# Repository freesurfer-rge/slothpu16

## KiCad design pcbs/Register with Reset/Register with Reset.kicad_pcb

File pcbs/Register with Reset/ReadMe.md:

# Register with Reset

This is a 16-bit register, which will reset to zero on power on, or when the RESET line is pulled low.

Notes:

- Diodes (but not LEDs) appeared to be back-to-front in placement files
- Had to resize vias, since smallest ones are extra cost
- RESET needs to be low for about 0.1 sec to be effective. On return high, need to wait about 0.1 sec before register will be effective again
- There is still some oddness around the RESET line on the r1 board; I've noticed that when the final test completes, there's often one LED left on. But a manual reset gets rid of it

Errata:

- The CLK and RESET lines block each other, since the clock signal to the registers is the result of ORing the two (well, delay-inverted-output for RESET) together. UPDATE for *r1*, the RESET and CLK lines are ANDed together to produce the 'clock' side of the reset, so a low on RESET will inhibit the clock, and should largely avoid this issue.

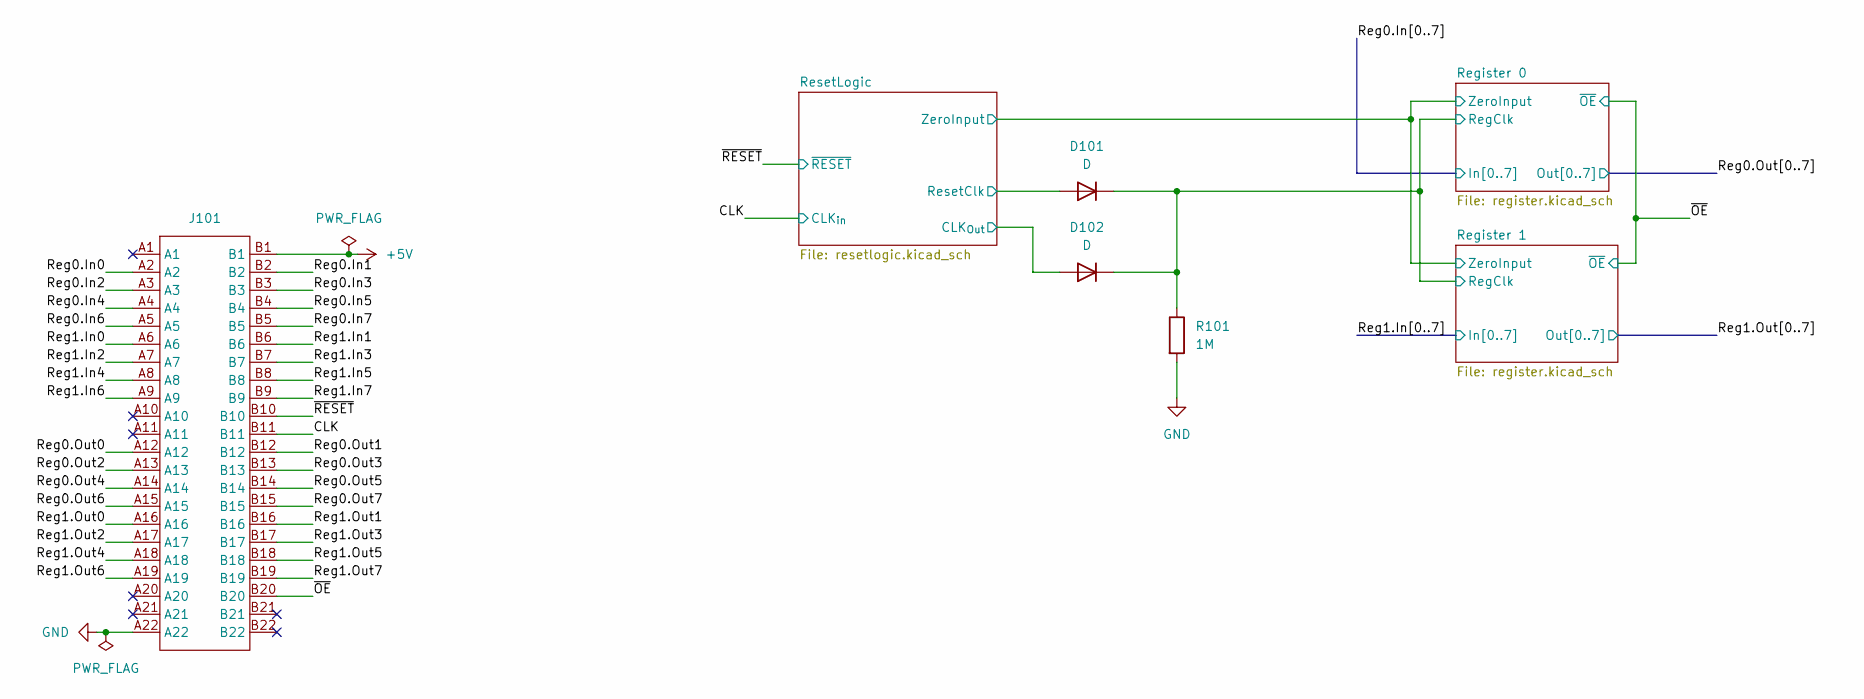
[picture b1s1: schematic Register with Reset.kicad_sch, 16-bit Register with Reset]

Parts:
D101, D102: D; D_SOD-123; LCSC C7420318
J101: TE-5530843-4-Edge
R101: 1M; R_0603_1608Metric; LCSC C22935

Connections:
+5V: J101.B1; also elsewhere on the board
/CLK: J101.B11; also elsewhere on the board
/Reg0.In0: J101.A2; also elsewhere on the board
/Reg0.In1: J101.B2; also elsewhere on the board
/Reg0.In2: J101.A3; also elsewhere on the board
/Reg0.In3: J101.B3; also elsewhere on the board
/Reg0.In4: J101.A4; also elsewhere on the board
/Reg0.In5: J101.B4; also elsewhere on the board
/Reg0.In6: J101.A5; also elsewhere on the board
/Reg0.In7: J101.B5; also elsewhere on the board
/Reg0.Out0: J101.A12; also elsewhere on the board
/Reg0.Out1: J101.B12; also elsewhere on the board
/Reg0.Out2: J101.A13; also elsewhere on the board
/Reg0.Out3: J101.B13; also elsewhere on the board
/Reg0.Out4: J101.A14; also elsewhere on the board
/Reg0.Out5: J101.B14; also elsewhere on the board
/Reg0.Out6: J101.A15; also elsewhere on the board
/Reg0.Out7: J101.B15; also elsewhere on the board
/Reg1.In0: J101.A6; also elsewhere on the board
/Reg1.In1: J101.B6; also elsewhere on the board
/Reg1.In2: J101.A7; also elsewhere on the board
/Reg1.In3: J101.B7; also elsewhere on the board
/Reg1.In4: J101.A8; also elsewhere on the board
/Reg1.In5: J101.B8; also elsewhere on the board
/Reg1.In6: J101.A9; also elsewhere on the board
/Reg1.In7: J101.B9; also elsewhere on the board
/Reg1.Out0: J101.A16; also elsewhere on the board
/Reg1.Out1: J101.B16; also elsewhere on the board
/Reg1.Out2: J101.A17; also elsewhere on the board
/Reg1.Out3: J101.B17; also elsewhere on the board
/Reg1.Out4: J101.A18; also elsewhere on the board
/Reg1.Out5: J101.B18; also elsewhere on the board
/Reg1.Out6: J101.A19; also elsewhere on the board
/Reg1.Out7: J101.B19; also elsewhere on the board
/Register 0/RegClk: D101.1 (K), D102.1 (K), R101.1; also elsewhere on the board
/ResetLogic/CLK_{Out}: D102.2 (A); also elsewhere on the board
/ResetLogic/ResetClk: D101.2 (A); also elsewhere on the board
/~OE: J101.B20; also elsewhere on the board
/~RESET: J101.B10; also elsewhere on the board
GND: J101.A22, R101.2; also elsewhere on the board

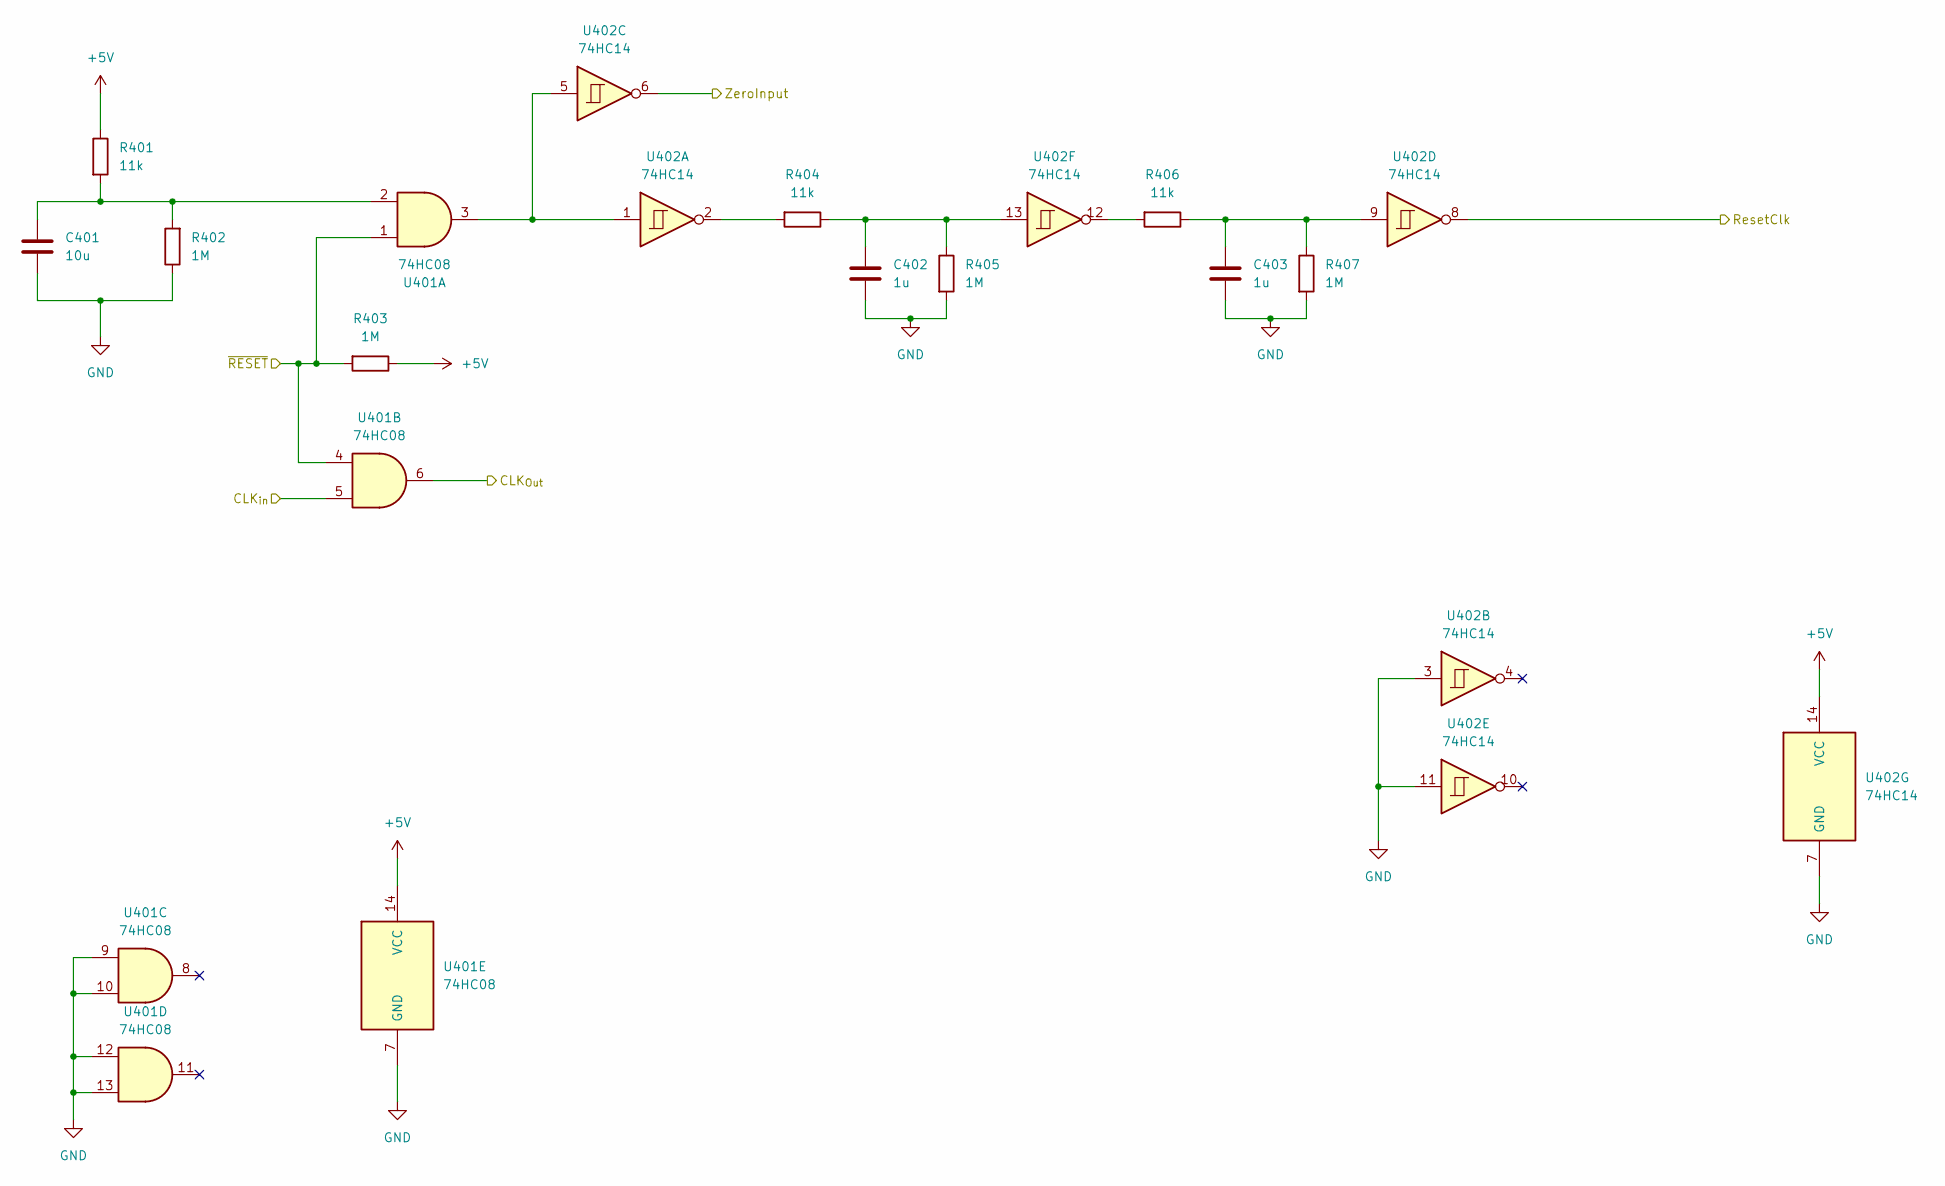
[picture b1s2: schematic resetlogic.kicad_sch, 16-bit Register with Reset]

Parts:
C401: 10u; C_0603_1608Metric; LCSC C19702
C402, C403: 1u; C_0603_1608Metric; LCSC C15849
R401, R404, R406: 11k; R_0603_1608Metric; LCSC C25950
R402, R403, R405, R407: 1M; R_0603_1608Metric; LCSC C22935
U401: 74HC08; SOIC-14_3.9x8.7mm_P1.27mm; LCSC C5593
U402: 74HC14; SOIC-14_3.9x8.7mm_P1.27mm; LCSC C5605

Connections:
+5V: R401.1, R403.1, U401.14 (VCC), U402.14 (VCC); also elsewhere on the board
/CLK: U401.5; also elsewhere on the board
/Register 0/ZeroInput: U402.6; also elsewhere on the board
/ResetLogic/CLK_{Out}: U401.6; also elsewhere on the board
/ResetLogic/ResetClk: U402.8; also elsewhere on the board
/~RESET: R403.2, U401.1, U401.4; also elsewhere on the board
GND: C401.2, C402.2, C403.2, R402.1, R405.2, R407.2, U401.7 (GND), U401.9, U401.10, U401.12, U401.13, U402.3, U402.7 (GND), U402.11; also elsewhere on the board
unnamed: C401.1, R401.2, R402.2, U401.2
unnamed: C402.1, R404.1, R405.1, U402.13
unnamed: C403.1, R406.1, R407.1, U402.9
unnamed: R404.2, U402.2
unnamed: R406.2, U402.12
unnamed: U401.3, U402.1, U402.5

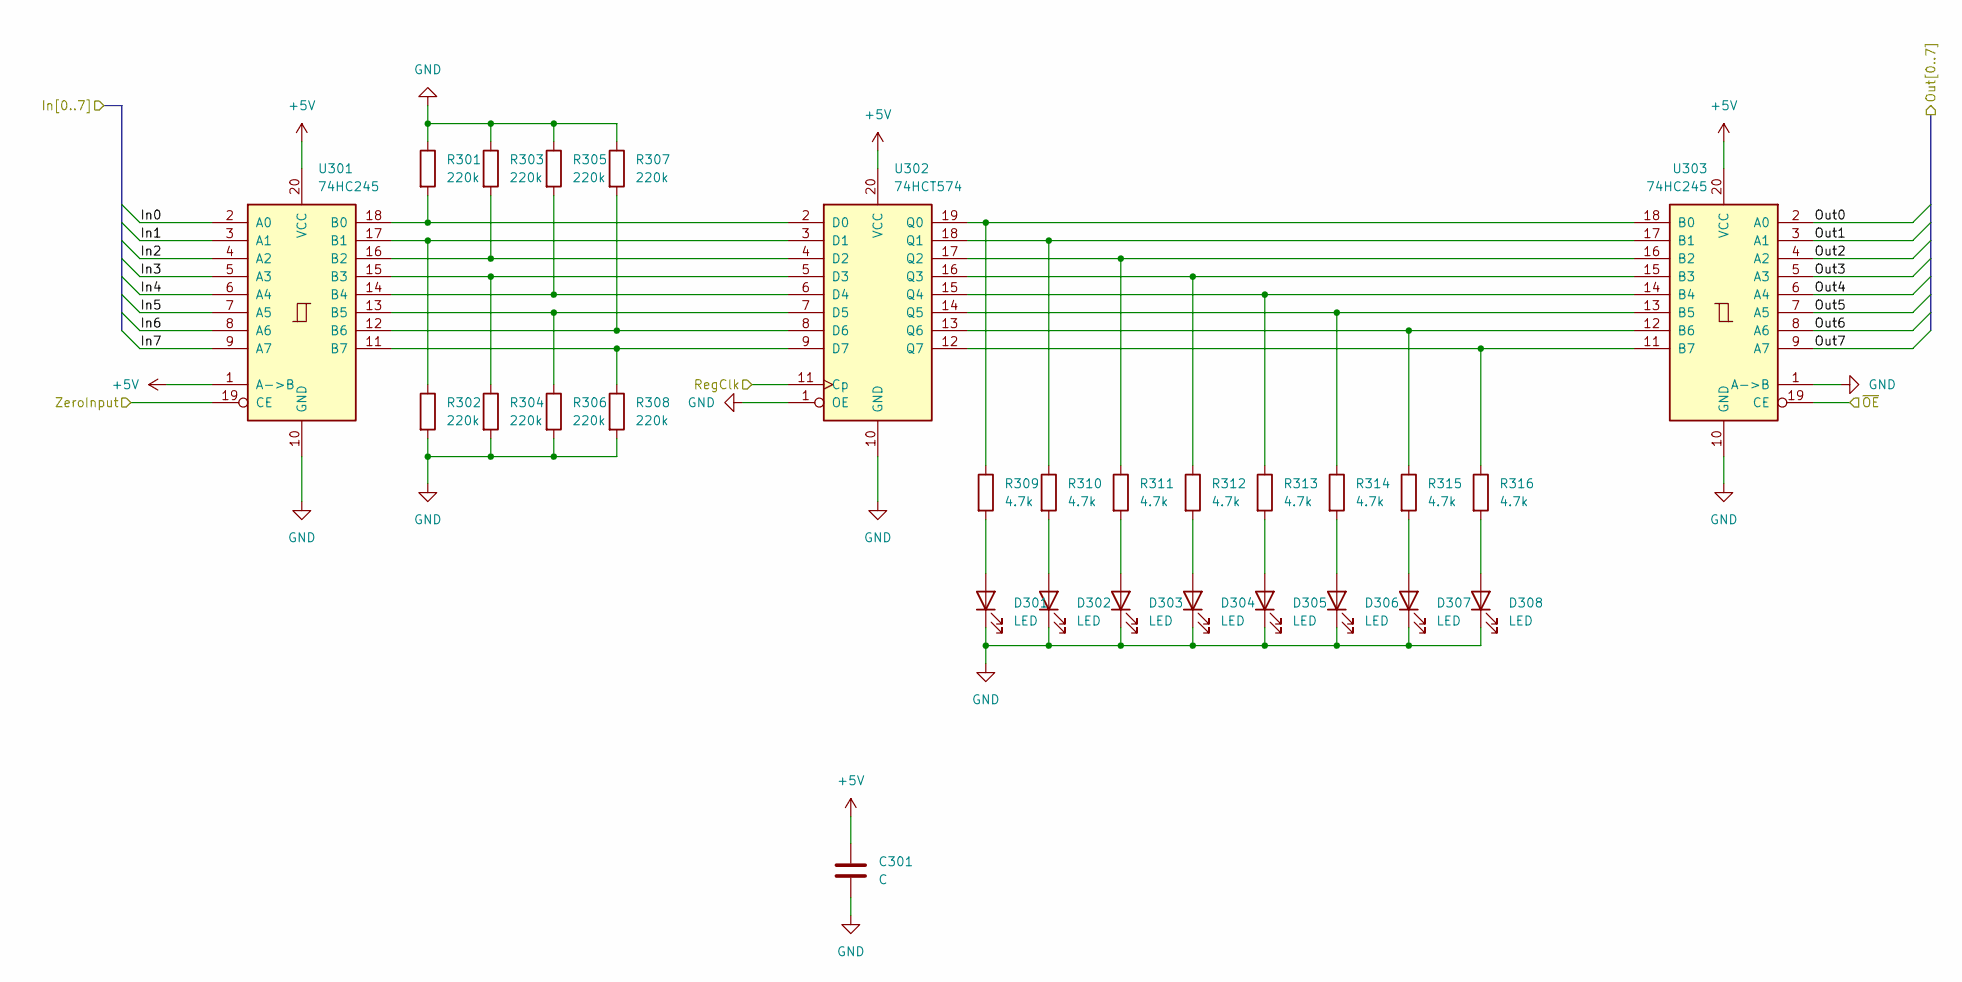
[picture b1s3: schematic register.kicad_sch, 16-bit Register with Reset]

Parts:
C301: C; C_0603_1608Metric; LCSC C14663
D301, D302, D303, D304, D305, D306, D307, D308: LED; LED_0603_1608Metric; LCSC C2290
R301, R302, R303, R304, R305, R306, R307, R308: 220k; R_0603_1608Metric; LCSC C22961
R309, R310, R311, R312, R313, R314, R315, R316: 4.7k; R_0603_1608Metric; LCSC C23162
U301, U303: 74HC245; SOIC-20W_7.5x12.8mm_P1.27mm; LCSC C5625
U302: 74HCT574; DIP-20_W7.62mm_Socket

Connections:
+5V: C301.1, U301.1 (A->B), U301.20 (VCC), U302.20 (VCC), U303.20 (VCC); also elsewhere on the board
/Reg1.In0: U301.2 (A0); also elsewhere on the board
/Reg1.In1: U301.3 (A1); also elsewhere on the board
/Reg1.In2: U301.4 (A2); also elsewhere on the board
/Reg1.In3: U301.5 (A3); also elsewhere on the board
/Reg1.In4: U301.6 (A4); also elsewhere on the board
/Reg1.In5: U301.7 (A5); also elsewhere on the board
/Reg1.In6: U301.8 (A6); also elsewhere on the board
/Reg1.In7: U301.9 (A7); also elsewhere on the board
/Reg1.Out0: U303.2 (A0); also elsewhere on the board
/Reg1.Out1: U303.3 (A1); also elsewhere on the board
/Reg1.Out2: U303.4 (A2); also elsewhere on the board
/Reg1.Out3: U303.5 (A3); also elsewhere on the board
/Reg1.Out4: U303.6 (A4); also elsewhere on the board
/Reg1.Out5: U303.7 (A5); also elsewhere on the board
/Reg1.Out6: U303.8 (A6); also elsewhere on the board
/Reg1.Out7: U303.9 (A7); also elsewhere on the board
/Register 0/RegClk: U302.11 (Cp); also elsewhere on the board
/Register 0/ZeroInput: U301.19 (CE); also elsewhere on the board
/~OE: U303.19 (CE); also elsewhere on the board
GND: C301.2, D301.1 (K), D302.1 (K), D303.1 (K), D304.1 (K), D305.1 (K), D306.1 (K), D307.1 (K), D308.1 (K), R301.1, R302.2, R303.1, R304.2, R305.1, R306.2, R307.1, R308.2, U301.10 (GND), U302.1 (OE), U302.10 (GND), U303.1 (A->B), U303.10 (GND); also elsewhere on the board
unnamed: D301.2 (A), R309.2
unnamed: D302.2 (A), R310.2
unnamed: D303.2 (A), R311.2
unnamed: D304.2 (A), R312.2
unnamed: D305.2 (A), R313.2
unnamed: D306.2 (A), R314.2
unnamed: D307.2 (A), R315.2
unnamed: D308.2 (A), R316.2
unnamed: R301.2, U301.18 (B0), U302.2 (D0)
unnamed: R302.1, U301.17 (B1), U302.3 (D1)
unnamed: R303.2, U301.16 (B2), U302.4 (D2)
unnamed: R304.1, U301.15 (B3), U302.5 (D3)
unnamed: R305.2, U301.14 (B4), U302.6 (D4)
unnamed: R306.1, U301.13 (B5), U302.7 (D5)
unnamed: R307.2, U301.12 (B6), U302.8 (D6)
unnamed: R308.1, U301.11 (B7), U302.9 (D7)
unnamed: R309.1, U302.19 (Q0), U303.18 (B0)
unnamed: R310.1, U302.18 (Q1), U303.17 (B1)
unnamed: R311.1, U302.17 (Q2), U303.16 (B2)
unnamed: R312.1, U302.16 (Q3), U303.15 (B3)
unnamed: R313.1, U302.15 (Q4), U303.14 (B4)
unnamed: R314.1, U302.14 (Q5), U303.13 (B5)
unnamed: R315.1, U302.13 (Q6), U303.12 (B6)
unnamed: R316.1, U302.12 (Q7), U303.11 (B7)

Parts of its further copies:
C201: C; C_0603_1608Metric; LCSC C14663
D201, D202, D203, D204, D205, D206, D207, D208: LED; LED_0603_1608Metric; LCSC C2290
R201, R202, R203, R204, R205, R206, R207, R208: 220k; R_0603_1608Metric; LCSC C22961
R209, R210, R211, R212, R213, R214, R215, R216: 4.7k; R_0603_1608Metric; LCSC C23162
U201, U203: 74HC245; SOIC-20W_7.5x12.8mm_P1.27mm; LCSC C5625
U202: 74HCT574; DIP-20_W7.62mm_Socket

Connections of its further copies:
+5V: C201.1, U201.1 (A->B), U201.20 (VCC), U202.20 (VCC), U203.20 (VCC); also elsewhere on the board
/Reg0.In0: U201.2 (A0); also elsewhere on the board
/Reg0.In1: U201.3 (A1); also elsewhere on the board
/Reg0.In2: U201.4 (A2); also elsewhere on the board
/Reg0.In3: U201.5 (A3); also elsewhere on the board
/Reg0.In4: U201.6 (A4); also elsewhere on the board
/Reg0.In5: U201.7 (A5); also elsewhere on the board
/Reg0.In6: U201.8 (A6); also elsewhere on the board
/Reg0.In7: U201.9 (A7); also elsewhere on the board
/Reg0.Out0: U203.2 (A0); also elsewhere on the board
/Reg0.Out1: U203.3 (A1); also elsewhere on the board
/Reg0.Out2: U203.4 (A2); also elsewhere on the board
/Reg0.Out3: U203.5 (A3); also elsewhere on the board
/Reg0.Out4: U203.6 (A4); also elsewhere on the board
/Reg0.Out5: U203.7 (A5); also elsewhere on the board
/Reg0.Out6: U203.8 (A6); also elsewhere on the board
/Reg0.Out7: U203.9 (A7); also elsewhere on the board
/Register 0/RegClk: U202.11 (Cp); also elsewhere on the board
/Register 0/ZeroInput: U201.19 (CE); also elsewhere on the board
/~OE: U203.19 (CE); also elsewhere on the board
GND: C201.2, D201.1 (K), D202.1 (K), D203.1 (K), D204.1 (K), D205.1 (K), D206.1 (K), D207.1 (K), D208.1 (K), R201.1, R202.2, R203.1, R204.2, R205.1, R206.2, R207.1, R208.2, U201.10 (GND), U202.1 (OE), U202.10 (GND), U203.1 (A->B), U203.10 (GND); also elsewhere on the board
unnamed: D201.2 (A), R209.2
unnamed: D202.2 (A), R210.2
unnamed: D203.2 (A), R211.2
unnamed: D204.2 (A), R212.2
unnamed: D205.2 (A), R213.2
unnamed: D206.2 (A), R214.2
unnamed: D207.2 (A), R215.2
unnamed: D208.2 (A), R216.2
unnamed: R201.2, U201.18 (B0), U202.2 (D0)
unnamed: R202.1, U201.17 (B1), U202.3 (D1)
unnamed: R203.2, U201.16 (B2), U202.4 (D2)
unnamed: R204.1, U201.15 (B3), U202.5 (D3)
unnamed: R205.2, U201.14 (B4), U202.6 (D4)
unnamed: R206.1, U201.13 (B5), U202.7 (D5)
unnamed: R207.2, U201.12 (B6), U202.8 (D6)
unnamed: R208.1, U201.11 (B7), U202.9 (D7)
unnamed: R209.1, U202.19 (Q0), U203.18 (B0)
unnamed: R210.1, U202.18 (Q1), U203.17 (B1)
unnamed: R211.1, U202.17 (Q2), U203.16 (B2)
unnamed: R212.1, U202.16 (Q3), U203.15 (B3)
unnamed: R213.1, U202.15 (Q4), U203.14 (B4)
unnamed: R214.1, U202.14 (Q5), U203.13 (B5)
unnamed: R215.1, U202.13 (Q6), U203.12 (B6)
unnamed: R216.1, U202.12 (Q7), U203.11 (B7)

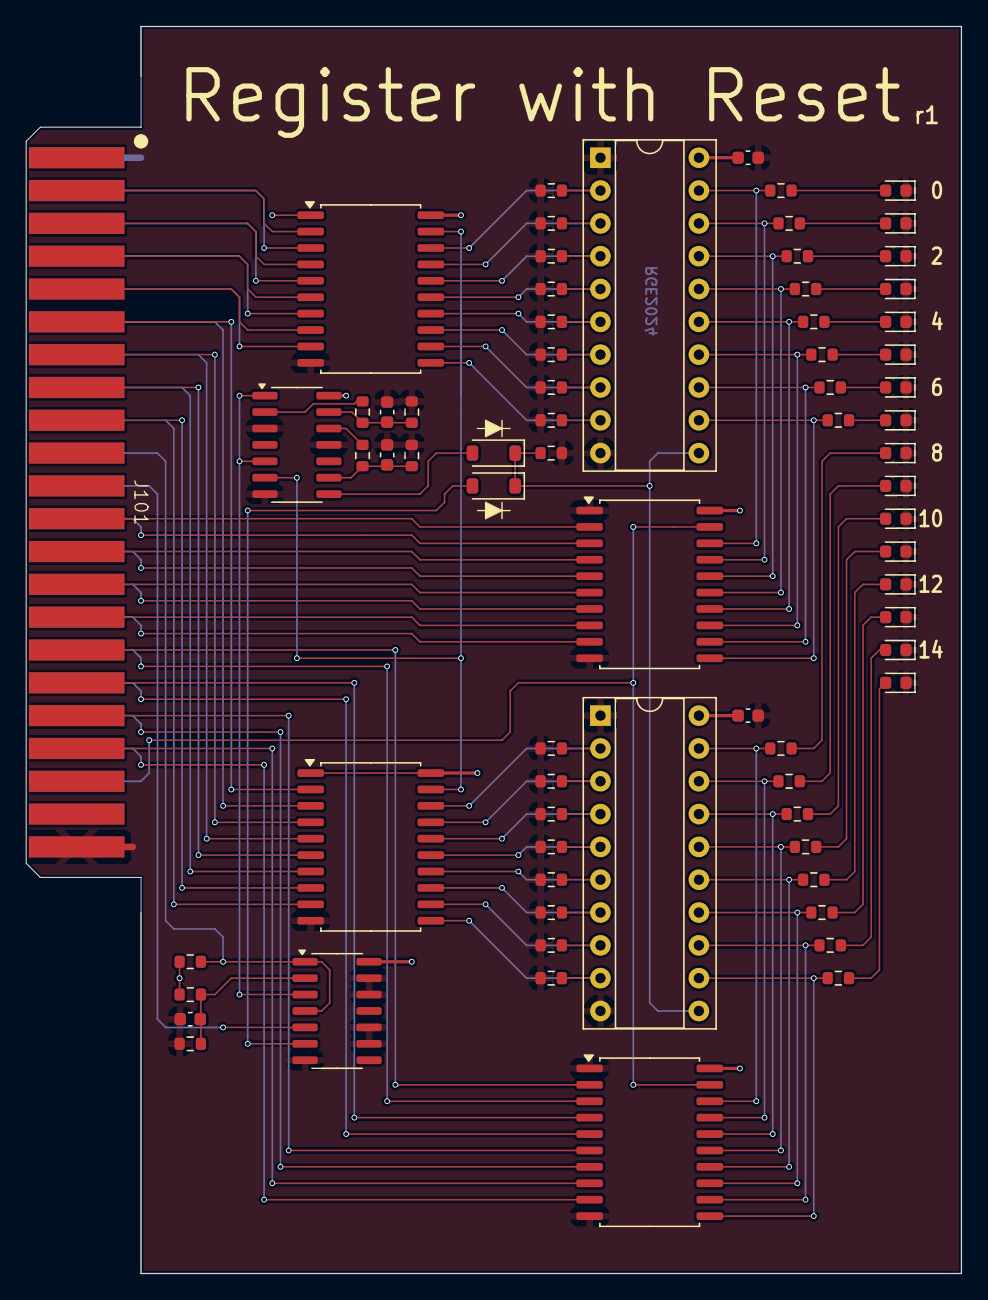
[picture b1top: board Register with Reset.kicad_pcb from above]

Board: 2 copper layers, 72.4 x 96.5 mm, 72 parts (0 on the bottom side), 95 nets.

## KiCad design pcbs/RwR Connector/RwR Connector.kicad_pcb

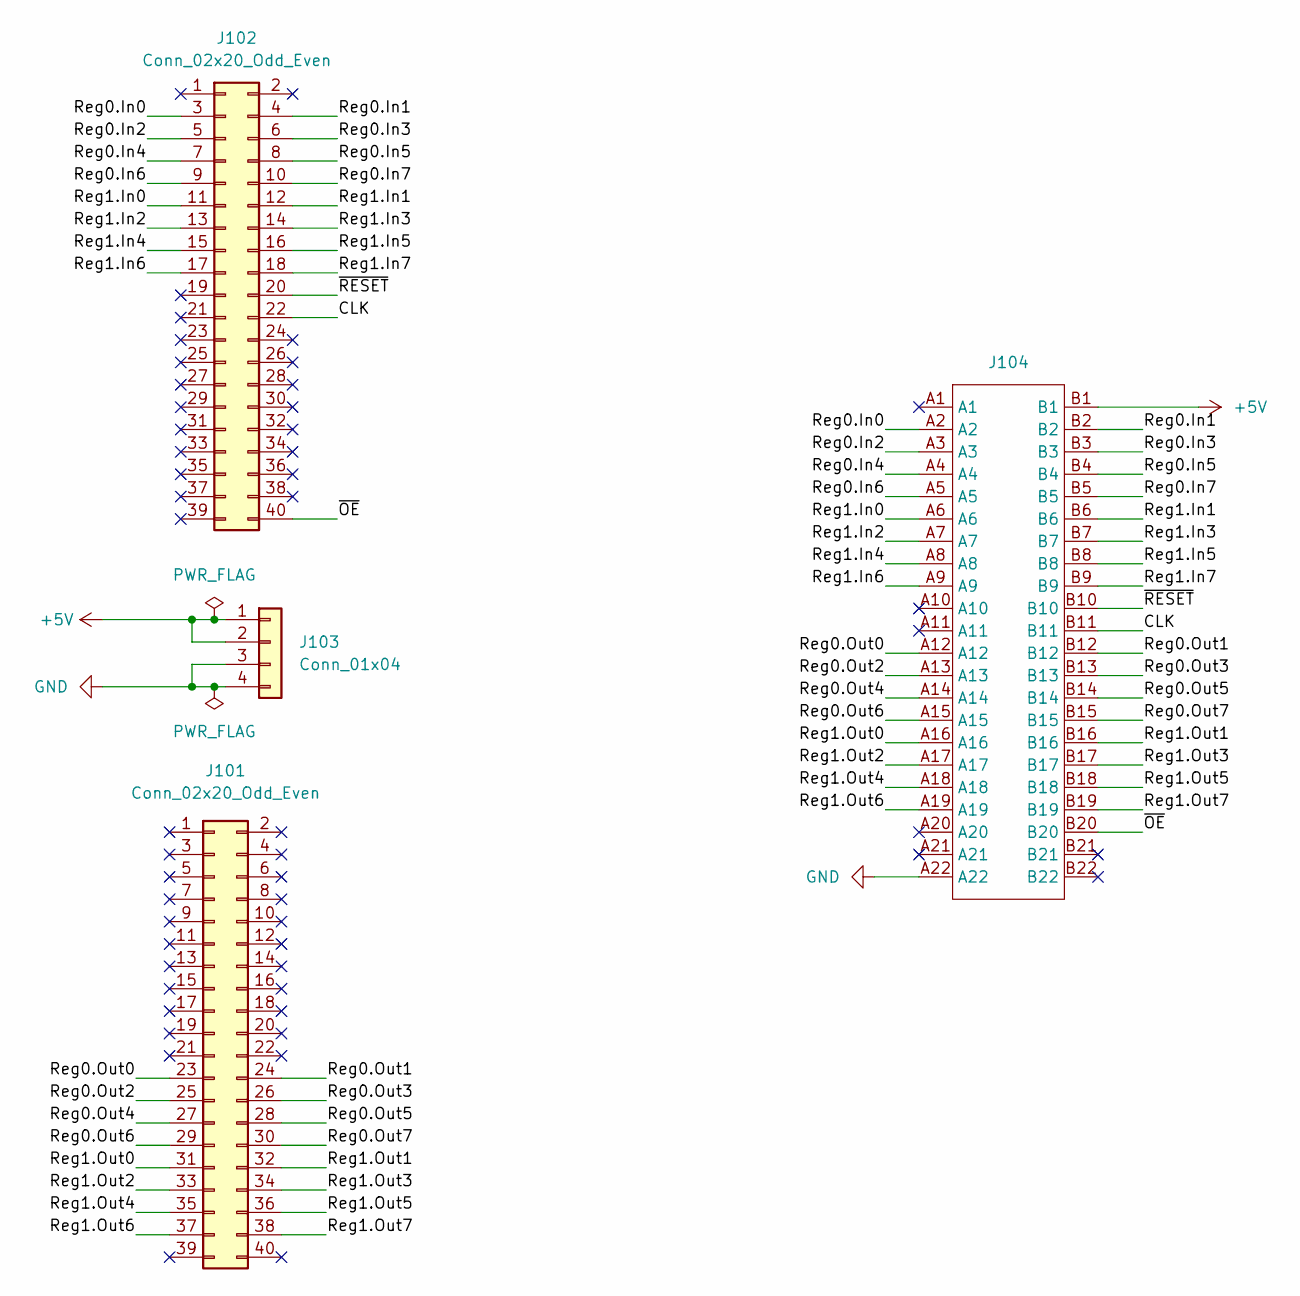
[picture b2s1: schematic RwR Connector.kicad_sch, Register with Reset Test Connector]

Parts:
J101, J102: Conn_02x20_Odd_Even; PinHeader_2x20_P2.54mm_Vertical
J103: Conn_01x04; PinHeader_1x04_P2.54mm_Vertical
J104: TE-5530843-4-Mount

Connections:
+5V: J103.1, J103.2, J104.B1
/CLK: J102.22, J104.B11
/Reg0.In0: J102.3, J104.A2
/Reg0.In1: J102.4, J104.B2
/Reg0.In2: J102.5, J104.A3
/Reg0.In3: J102.6, J104.B3
/Reg0.In4: J102.7, J104.A4
/Reg0.In5: J102.8, J104.B4
/Reg0.In6: J102.9, J104.A5
/Reg0.In7: J102.10, J104.B5
/Reg0.Out0: J101.23, J104.A12
/Reg0.Out1: J101.24, J104.B12
/Reg0.Out2: J101.25, J104.A13
/Reg0.Out3: J101.26, J104.B13
/Reg0.Out4: J101.27, J104.A14
/Reg0.Out5: J101.28, J104.B14
/Reg0.Out6: J101.29, J104.A15
/Reg0.Out7: J101.30, J104.B15
/Reg1.In0: J102.11, J104.A6
/Reg1.In1: J102.12, J104.B6
/Reg1.In2: J102.13, J104.A7
/Reg1.In3: J102.14, J104.B7
/Reg1.In4: J102.15, J104.A8
/Reg1.In5: J102.16, J104.B8
/Reg1.In6: J102.17, J104.A9
/Reg1.In7: J102.18, J104.B9
/Reg1.Out0: J101.31, J104.A16
/Reg1.Out1: J101.32, J104.B16
/Reg1.Out2: J101.33, J104.A17
/Reg1.Out3: J101.34, J104.B17
/Reg1.Out4: J101.35, J104.A18
/Reg1.Out5: J101.36, J104.B18
/Reg1.Out6: J101.37, J104.A19
/Reg1.Out7: J101.38, J104.B19
/~OE: J102.40, J104.B20
/~RESET: J102.20, J104.B10
GND: J103.3, J103.4, J104.A22

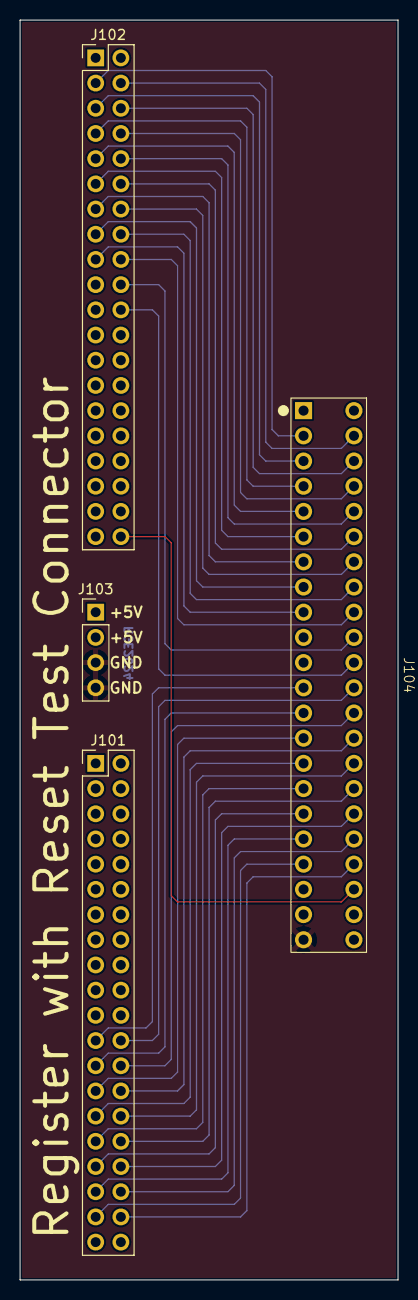
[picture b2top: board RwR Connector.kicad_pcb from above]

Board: 2 copper layers, 38.1 x 127.0 mm, 4 parts (0 on the bottom side), 37 nets.
